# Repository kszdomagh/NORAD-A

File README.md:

# NORAD-A

NORAD-A to minimalistyczny symulator, w którym gracz wciela się w operatora systemu radarowego w trakcie narastającego kryzysu nuklearnego. Zadaniem gracza jest monitorowanie przestrzeni powietrznej, identyfikacja potencjalnych zagrożeń i szybkie podejmowanie decyzji w oparciu o niepełne informacje. Cały interfejs gry wyświetlany jest na oscyloskopie pracującym w trybie XY, podkreślając surowy charakter rozgrywki.

# Sterowanie

## Przełączniki
SW15 - kontroluje wyświetlanie ekranu gry z mapą Stanów Zjednoczonych;

SW14 - kontroluje wyświetlanie logo kierunku MTM (https://www.mtm.agh.edu.pl/);

SW0 - reset;

## Przyciski

btnU, btnD - przyciski sterują pionowym ruchem kursora (odpowiednio UP, DOWN);

btnL, btnR - przyciski sterują poziomym ruchem kursora (odpowiednio LEFT, RIGHT);

btnC - przycisk "środkowy" wystrzeliwuje rakietę.

# Konfiguracja sprzętu
Do gry potrzebny jest oscyloskop (najlepiej analogowy) z conajmniej dwoma kanałami oraz trybem XY, dwa przetworniki cyfrowo-analogowe podłączone do portów JB oraz JC.

# Film
Film pokazujący działanie gry znajduje się pod następującym linkiem:
https://youtu.be/zArHo4Ynv9o?feature=shared

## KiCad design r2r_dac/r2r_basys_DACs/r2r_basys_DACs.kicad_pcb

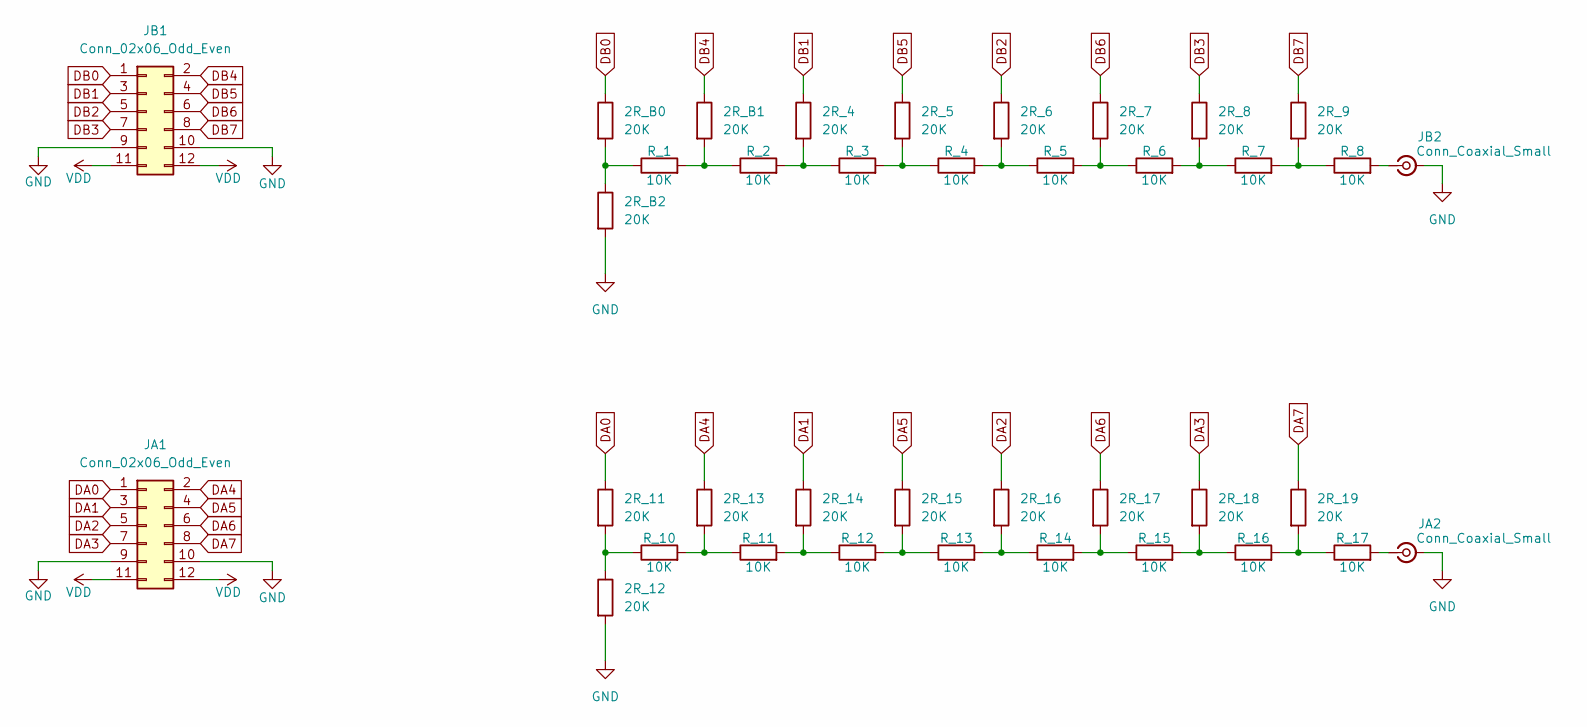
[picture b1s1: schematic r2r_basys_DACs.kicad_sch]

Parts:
2R_4, 2R_5, 2R_6, 2R_7, 2R_8, 2R_9, 2R_11, 2R_12, 2R_13, 2R_14, 2R_15, 2R_16, 2R_17, 2R_18, 2R_19, 2R_B0, 2R_B1, 2R_B2: 20K; R_0805_2012Metric_Pad1.20x1.40mm_HandSolder
JA1: Conn_02x06_Odd_Even; PinHeader_2x06_P2.54mm_Vertical
JA2: Conn_Coaxial_Small; SMA_Wurth_60312002114503_Vertical
JB1: Conn_02x06_Odd_Even; PinHeader_2x06_P2.54mm_Vertical
JB2: Conn_Coaxial_Small; SMA_Wurth_60312002114503_Vertical
R_1, R_2, R_3, R_4, R_5, R_6, R_7, R_8, R_10, R_11, R_12, R_13, R_14, R_15, R_16, R_17: 10K; R_0805_2012Metric_Pad1.20x1.40mm_HandSolder

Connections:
DA0: 2R_11.1, JA1.1
DA1: 2R_14.1, JA1.3
DA2: 2R_16.1, JA1.5
DA3: 2R_18.1, JA1.7
DA4: 2R_13.1, JA1.2
DA5: 2R_15.1, JA1.4
DA6: 2R_17.1, JA1.6
DA7: 2R_19.1, JA1.8
DB0: 2R_B0.1, JB1.1
DB1: 2R_4.1, JB1.3
DB2: 2R_6.1, JB1.5
DB3: 2R_8.1, JB1.7
DB4: 2R_B1.1, JB1.2
DB5: 2R_5.1, JB1.4
DB6: 2R_7.1, JB1.6
DB7: 2R_9.1, JB1.8
GND: 2R_12.2, 2R_B2.2, JA1.9, JA1.10, JA2.2 (Ext), JB1.9, JB1.10, JB2.2 (Ext)
unnamed: 2R_4.2, R_2.2, R_3.1
unnamed: 2R_5.2, R_3.2, R_4.1
unnamed: 2R_6.2, R_4.2, R_5.1
unnamed: 2R_7.2, R_5.2, R_6.1
unnamed: 2R_8.2, R_6.2, R_7.1
unnamed: 2R_9.2, R_7.2, R_8.1
unnamed: 2R_11.2, 2R_12.1, R_10.1
unnamed: 2R_13.2, R_10.2, R_11.1
unnamed: 2R_14.2, R_11.2, R_12.1
unnamed: 2R_15.2, R_12.2, R_13.1
unnamed: 2R_16.2, R_13.2, R_14.1
unnamed: 2R_17.2, R_14.2, R_15.1
unnamed: 2R_18.2, R_15.2, R_16.1
unnamed: 2R_19.2, R_16.2, R_17.1
unnamed: 2R_B0.2, 2R_B2.1, R_1.1
unnamed: 2R_B1.2, R_1.2, R_2.1
unnamed: JA2.1 (In), R_17.2
unnamed: JB2.1 (In), R_8.2
VDD: JA1.11, JA1.12, JB1.11, JB1.12

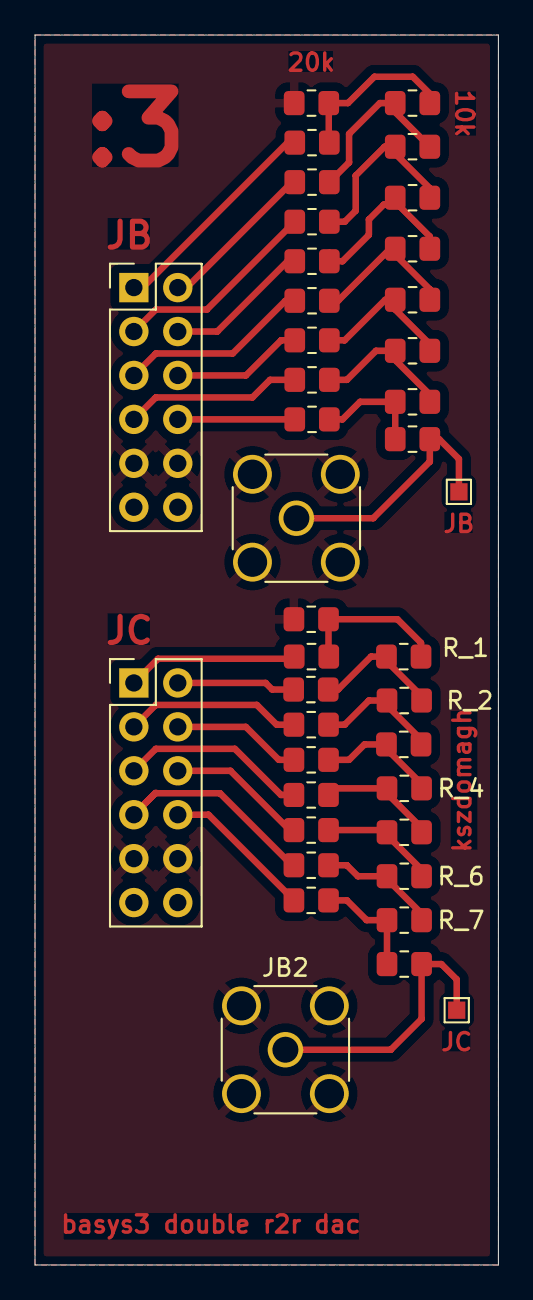
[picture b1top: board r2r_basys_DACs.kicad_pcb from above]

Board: 2 copper layers, 26.8 x 71.1 mm, 38 parts (0 on the bottom side), 36 nets.

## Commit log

2025-04-18 WHOOOHO DAC ON X CHANNEL WORKS MIRACLE
2025-04-19 y channel dac done i guess
2025-04-19 dac y
2025-04-19 y axis changes
2025-04-19 more dac debugging and fixes
2025-04-19 x dac and y dac synced - work
2025-04-19 frame drawing
2025-04-19 frame changes
2025-04-19 square frame drawing optimalization for 40MEG analog osc
2025-04-29 went back
2025-04-29 fixed kinda
2025-04-29 fixed square drawing, started working on vector_display_tb
2025-04-30 added draw_line algo module
2025-04-30 added line drawing algo - not done
2025-05-01 draw line tb
2025-05-03 verilog module for line drawing
2025-05-04 did a lot of work on using ram to display lines and points - not functional yet
2025-05-28 ehhhh
2025-05-28 started working on draw vector master - updatdes/ moved memory to top rtl
2025-05-29 edit - fsm for vector master
2025-05-29 started fixes are vector dfisplay
2025-05-29 kinda fixed draw vector master tb
2025-05-29 drawing works - need to implement memory looping
2025-05-31 tb for whole top rtl
2025-07-30 fsm vector manage module added (between dac and memory)
2025-07-30 tb for vector manage - chyba dziala
2025-07-30 vector manage - looping from memory works
2025-07-30 tb for vector manage fully works - :3
2025-08-02 some work idk
2025-08-05 fixed line drawing - it draws good but there is end/start coordinations swap
2025-08-05 fixed top vector display
2025-08-12 works on hardware; minimal number of error - glitches check issue in github
2025-08-12 idkk
2025-08-13 ROM USA MAP and outline
2025-08-13 added memory manage and getting ready to implement RAM
2025-08-13 mouse and RAM added
2025-08-14 fixed issue with memory manage
2025-08-14 changed mouse module
2025-08-15 added timer cluster, enemy control, added state in memory_manage and also changed back mouse control to the previous one
2025-08-15 organized control modules and added tb modules
2025-08-15 FIX FOR VECTOR MANAGE - CHANGED ALSO SOME STUFF
2025-08-16 dev tools added + fixes
2025-08-16 fixed end of memory line drawing glitch
2025-08-16 all 3 enemies added and showing up on screen
2025-08-16 changed enemy control module
2025-08-17 chamged game logic top
2025-08-20 added bases and logic for nuking
2025-08-21 r2r dac + some fixes to final game - now it semiworks
2025-08-23 timing setup fixed - changed 100MHz to 80MHz to fix
2025-08-24 screen manage added
2025-08-25 new DACs fixed and changes
2025-08-25 nuke fixes and reposition of bases
2025-08-26 enemy explosion fixes
2025-08-26 missile module tested and ready to switch with current wire control unit
2025-08-27 added flying missile - check for glitches
2025-08-27 bresenham module change to acomodate missile glitch
2025-08-27 working game
2025-08-27 added randomized enemies
2025-08-28 added comments to tb, tested tb and warnings are at all time low - ready
2025-08-30 flickering oscilo fixed for movie
2025-08-30 checklist
2025-08-30 kicad checklist
2025-08-31 final commit
